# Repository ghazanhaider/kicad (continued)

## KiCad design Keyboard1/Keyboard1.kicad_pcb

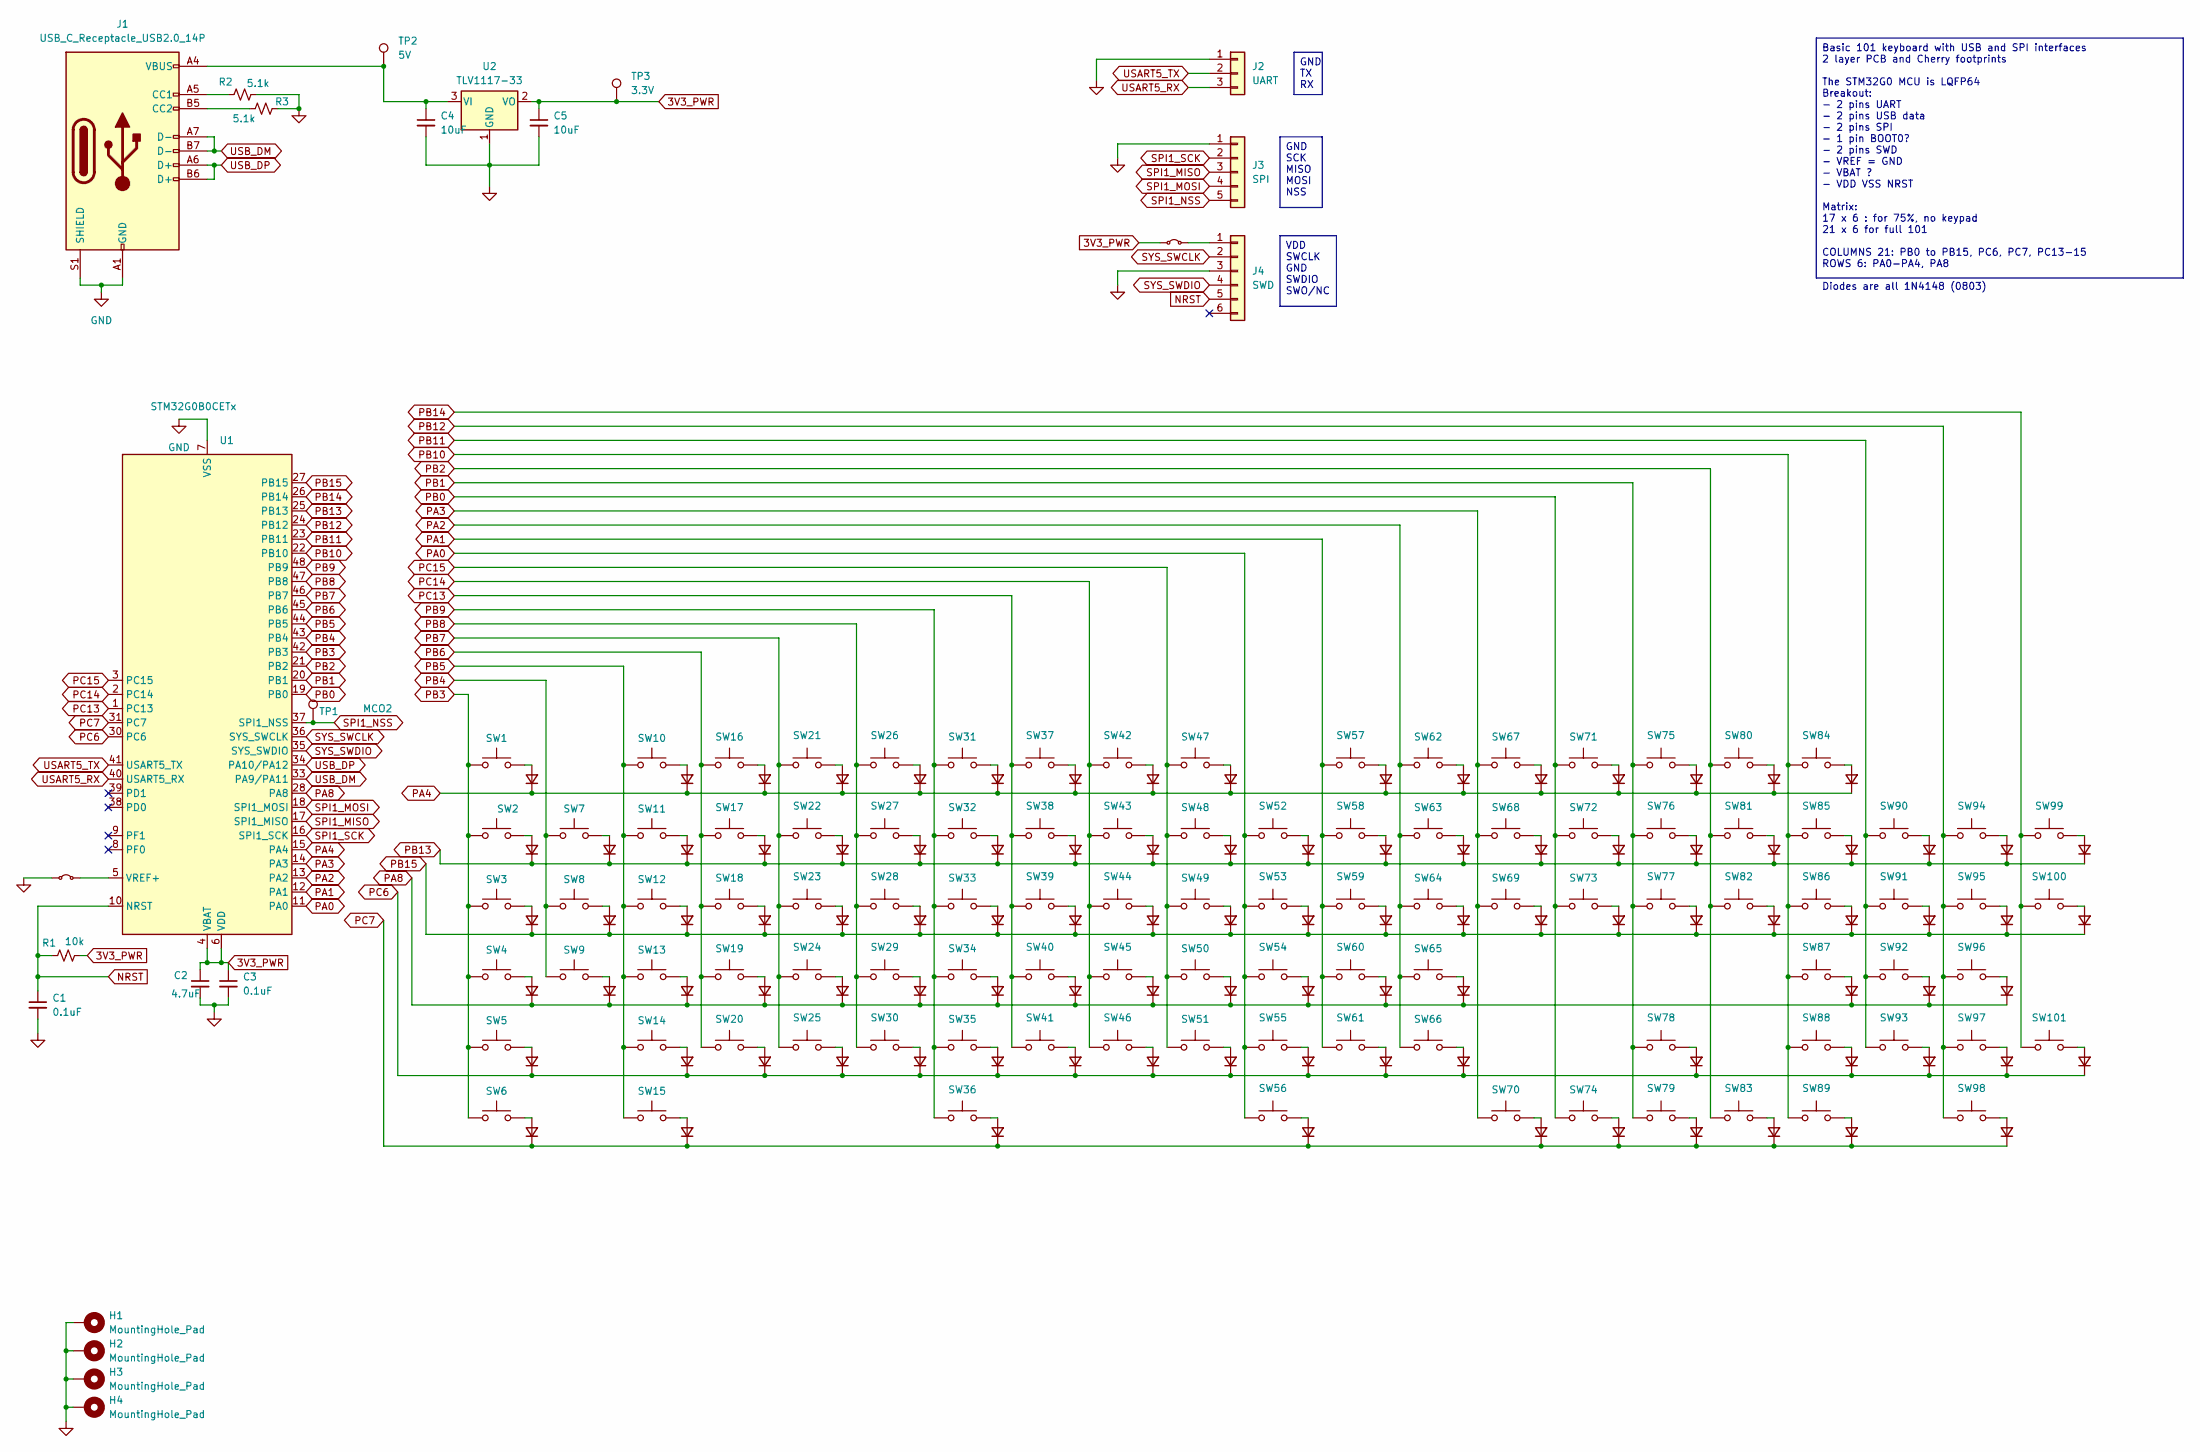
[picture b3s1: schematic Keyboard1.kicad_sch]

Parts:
C1, C3: 0.1uF; C_0603_1608Metric
C2: 4.7uF; C_0603_1608Metric
C4, C5: 10uF; C_0603_1608Metric
D1, D2, D3, D4, D5, D6, D7, D8, D9, D10, D11, D12, D13, D14, D15, D16, D17, D18, D19, D20, D21, D22, D23, D24, D25, D26, D27, D28, D29, D30, D31, D32, D33, D34, D35, D36, D37, D38, D39, D40, D41, D42, D43, D44, D45, D46, D47, D48, D49, D50, D51, D52, D53, D54, D55, D56, D57, D58, D59, D60, D61, D62, D63, D64, D65, D66, D67, D68, D69, D70, D71, D72, D73, D74, D75, D76, D77, D78, D79, D80, D81, D82, D83, D84, D85, D86, D87, D88, D89, D90, D91, D92, D93, D94, D95, D96, D97, D98, D99, D100, D101: D_Small; D_0805_2012Metric
H1, H2, H3, H4: MountingHole_Pad; MountingHole_2.7mm_M2.5_DIN965_Pad
J1: USB_C_Receptacle_USB2.0_14P; USB_C_Receptacle_GCT_USB4105-xx-A_16P_TopMnt_Horizontal
J2: UART; PinHeader_1x03_P2.54mm_Vertical
J3: SPI; PinHeader_1x05_P2.54mm_Vertical
J4: SWD; PinHeader_1x06_P2.54mm_Vertical
JP1, JP2: Jumper_2_Small_Bridged; SolderJumper-2_P1.3mm_Bridged_RoundedPad1.0x1.5mm
R1: 10k; R_0603_1608Metric
R2, R3: 5.1k; R_0603_1608Metric
SW1: SW_ESC?; SW_Cherry_MX_1.00u_PCB
SW2: SW_BACKTICK?; SW_Cherry_MX_1.00u_PCB
SW3: SW_TAB; SW_Cherry_MX_1.50u_PCB
SW4: SW_CAPS?; SW_Cherry_MX_1.75u_PCB
SW5: SW_LSHIFT?; SW_Cherry_MX_2.25u_PCB
SW6: SW_LCTRL?; SW_Cherry_MX_1.25u_PCB
SW7: SW_1; SW_Cherry_MX_1.00u_PCB
SW8: SW_Q; SW_Cherry_MX_1.00u_PCB
SW9: SW_A?; SW_Cherry_MX_1.00u_PCB
SW10: SW_F1; SW_Cherry_MX_1.00u_PCB
SW11: SW_2; SW_Cherry_MX_1.00u_PCB
SW12: SW_W; SW_Cherry_MX_1.00u_PCB
SW13: SW_S; SW_Cherry_MX_1.00u_PCB
SW14: SW_Z; SW_Cherry_MX_1.00u_PCB
SW15: SW_LALT?; SW_Cherry_MX_1.25u_PCB
SW16: SW_F2; SW_Cherry_MX_1.00u_PCB
SW17: SW_3; SW_Cherry_MX_1.00u_PCB
SW18: SW_E?; SW_Cherry_MX_1.00u_PCB
SW19: SW_D?; SW_Cherry_MX_1.00u_PCB
SW20: SW_X; SW_Cherry_MX_1.00u_PCB
SW21: SW_F3; SW_Cherry_MX_1.00u_PCB
SW22: SW_4; SW_Cherry_MX_1.00u_PCB
SW23: SW_R; SW_Cherry_MX_1.00u_PCB
SW24: SW_F?; SW_Cherry_MX_1.00u_PCB
SW25: SW_C?; SW_Cherry_MX_1.00u_PCB
SW26: SW_F4; SW_Cherry_MX_1.00u_PCB
SW27: SW_5; SW_Cherry_MX_1.00u_PCB
SW28: SW_T; SW_Cherry_MX_1.00u_PCB
SW29: SW_G?; SW_Cherry_MX_1.00u_PCB
SW30: SW_V; SW_Cherry_MX_1.00u_PCB
SW31: SW_F5; SW_Cherry_MX_1.00u_PCB
SW32: SW_6; SW_Cherry_MX_1.00u_PCB
SW33: SW_Y; SW_Cherry_MX_1.00u_PCB
SW34: SW_H?; SW_Cherry_MX_1.00u_PCB
SW35: SW_B?; SW_Cherry_MX_1.00u_PCB
SW36: SW_SPACE; SW_Cherry_MX_6.25u_PCB
SW37: SW_F6; SW_Cherry_MX_1.00u_PCB
SW38: SW_7; SW_Cherry_MX_1.00u_PCB
SW39: SW_U; SW_Cherry_MX_1.00u_PCB
SW40: SW_J?; SW_Cherry_MX_1.00u_PCB
SW41: SW_N?; SW_Cherry_MX_1.00u_PCB
SW42: SW_F7; SW_Cherry_MX_1.00u_PCB
SW43: SW_8; SW_Cherry_MX_1.00u_PCB
SW44: SW_I?; SW_Cherry_MX_1.00u_PCB
SW45: SW_K?; SW_Cherry_MX_1.00u_PCB
SW46: SW_M?; SW_Cherry_MX_1.00u_PCB
SW47: SW_F8; SW_Cherry_MX_1.00u_PCB
SW48: SW_9; SW_Cherry_MX_1.00u_PCB
SW49: SW_O; SW_Cherry_MX_1.00u_PCB
SW50: SW_L?; SW_Cherry_MX_1.00u_PCB
SW51: SW_COMMA?; SW_Cherry_MX_1.00u_PCB
SW52: SW_0; SW_Cherry_MX_1.00u_PCB
SW53: SW_P; SW_Cherry_MX_1.00u_PCB
SW54: SW_SCOLON; SW_Cherry_MX_1.00u_PCB
SW55: SW_DOT?; SW_Cherry_MX_1.00u_PCB
SW56: SW_RALT; SW_Cherry_MX_1.25u_PCB
SW57: SW_F9; SW_Cherry_MX_1.00u_PCB
SW58: SW_MINUS?; SW_Cherry_MX_1.00u_PCB
SW59: SW_LSQUARE?; SW_Cherry_MX_1.00u_PCB
SW60: SW_TICK; SW_Cherry_MX_1.00u_PCB
SW61: SW_SLASH; SW_Cherry_MX_1.00u_PCB
SW62: SW_F10; SW_Cherry_MX_1.00u_PCB
SW63: SW_PLUS; SW_Cherry_MX_1.00u_PCB
SW64: SW_RSQUARE; SW_Cherry_MX_1.00u_PCB
SW65: SW_ENTER?; SW_Cherry_MX_2.25u_PCB
SW66: SW_RSHIFT; SW_Cherry_MX_2.75u_PCB
SW67: SW_F11; SW_Cherry_MX_1.00u_PCB
SW68: SW_BACKSPACE?; SW_Cherry_MX_2.00u_PCB
SW69: SW_BSLASH?; SW_Cherry_MX_1.50u_PCB
SW70: SW_RCTRL; SW_Cherry_MX_1.25u_PCB
SW71: SW_F12; SW_Cherry_MX_1.00u_PCB
SW72: SW_INS?; SW_Cherry_MX_1.00u_PCB
SW73: SW_DELETE?; SW_Cherry_MX_1.00u_PCB
SW74: SW_LARROW?; SW_Cherry_MX_1.00u_PCB
SW75: SW_PRTSC; SW_Cherry_MX_1.00u_PCB
SW76: SW_HOME?; SW_Cherry_MX_1.00u_PCB
SW77: SW_END?; SW_Cherry_MX_1.00u_PCB
SW78: SW_UPARROW; SW_Cherry_MX_1.00u_PCB
SW79: SW_DARROW?; SW_Cherry_MX_1.00u_PCB
SW80: SW_SCRLK; SW_Cherry_MX_1.00u_PCB
SW81: SW_PGUP; SW_Cherry_MX_1.00u_PCB
SW82: SW_PGDN; SW_Cherry_MX_1.00u_PCB
SW83: SW_RARROW; SW_Cherry_MX_1.00u_PCB
SW84: SW_PAUSE; SW_Cherry_MX_1.00u_PCB
SW85: SW_NUMLOCK; SW_Cherry_MX_1.00u_PCB
SW86: SW_NP7; SW_Cherry_MX_1.00u_PCB
SW87: SW_NP4; SW_Cherry_MX_1.00u_PCB
SW88: SW_NP1; SW_Cherry_MX_1.00u_PCB
SW89: SW_NPINSERT; SW_Cherry_MX_2.00u_PCB
SW90: SW_NPSLASH; SW_Cherry_MX_1.00u_PCB
SW91: SW_NP8; SW_Cherry_MX_1.00u_PCB
SW92: SW_NP5; SW_Cherry_MX_1.00u_PCB
SW93: SW_NP2; SW_Cherry_MX_1.00u_PCB
SW94: SW_NPSTAR; SW_Cherry_MX_1.00u_PCB
SW95: SW_NP9; SW_Cherry_MX_1.00u_PCB
SW96: SW_NP6; SW_Cherry_MX_1.00u_PCB
SW97: SW_NP3; SW_Cherry_MX_1.00u_PCB
SW98: SW_NPDOT; SW_Cherry_MX_1.00u_PCB
SW99: SW_NPMINUS; SW_Cherry_MX_1.00u_PCB
SW100: SW_NPPLUS; SW_Cherry_MX_2.00u_Vertical_PCB
SW101: SW_NPENTER; SW_Cherry_MX_2.00u_Vertical_PCB
TP1: MCO2; TestPoint_Loop_D2.54mm_Drill1.5mm_Beaded
TP2: 5V; TestPoint_Loop_D2.54mm_Drill1.5mm_Beaded
TP3: 3.3V; TestPoint_Loop_D2.54mm_Drill1.5mm_Beaded
U1: STM32G0B0CETx; LQFP-48_7x7mm_P0.5mm
U2: TLV1117-33; SOT-223

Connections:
3V3_PWR: C2.1, C3.1, C5.1, JP2.1 (A), R1.2, TP3.1, U1.4 (VBAT), U1.6 (VDD), U2.2 (VO)
GND: C1.2, C2.2, C3.2, C4.2, C5.2, H1.1, H2.1, H3.1, H4.1, J1.A1 (GND), J1.A12 (GND), J1.B1 (GND), J1.B12 (GND), J1.S1 (SHIELD), J2.1, J3.1, J4.3, JP1.1 (A), R2.2, R3.2, U1.7 (VSS), U2.1 (GND)
NRST: C1.1, J4.5, R1.1, U1.10 (NRST)
unnamed: D1.2 (A), SW1.2
unnamed: D2.2 (A), SW2.2
unnamed: D3.2 (A), SW3.2
unnamed: D4.2 (A), SW4.2
unnamed: D5.2 (A), SW5.2
unnamed: D6.2 (A), SW6.2
unnamed: D7.2 (A), SW7.2
unnamed: D8.2 (A), SW8.2
unnamed: D9.2 (A), SW9.2
unnamed: D10.2 (A), SW10.2
unnamed: D11.2 (A), SW11.2
unnamed: D12.2 (A), SW12.2
unnamed: D13.2 (A), SW13.2
unnamed: D14.2 (A), SW14.2
unnamed: D15.2 (A), SW15.2
unnamed: D16.2 (A), SW16.2
unnamed: D17.2 (A), SW17.2
unnamed: D18.2 (A), SW18.2
unnamed: D19.2 (A), SW19.2
unnamed: D20.2 (A), SW20.2
unnamed: D21.2 (A), SW21.2
unnamed: D22.2 (A), SW22.2
unnamed: D23.2 (A), SW23.2
unnamed: D24.2 (A), SW24.2
unnamed: D25.2 (A), SW25.2
unnamed: D26.2 (A), SW26.2
unnamed: D27.2 (A), SW27.2
unnamed: D28.2 (A), SW28.2
unnamed: D29.2 (A), SW29.2
unnamed: D30.2 (A), SW30.2
unnamed: D31.2 (A), SW31.2
unnamed: D32.2 (A), SW32.2
unnamed: D33.2 (A), SW33.2
unnamed: D34.2 (A), SW34.2
unnamed: D35.2 (A), SW35.2
unnamed: D36.2 (A), SW36.2
unnamed: D37.2 (A), SW37.2
unnamed: D38.2 (A), SW38.2
unnamed: D39.2 (A), SW39.2
unnamed: D40.2 (A), SW40.2
unnamed: D41.2 (A), SW41.2
unnamed: D42.2 (A), SW42.2
unnamed: D43.2 (A), SW43.2
unnamed: D44.2 (A), SW44.2
unnamed: D45.2 (A), SW45.2
unnamed: D46.2 (A), SW46.2
unnamed: D47.2 (A), SW47.2
unnamed: D48.2 (A), SW48.2
unnamed: D49.2 (A), SW49.2
unnamed: D50.2 (A), SW50.2
unnamed: D51.2 (A), SW51.2
unnamed: D52.2 (A), SW52.2
unnamed: D53.2 (A), SW53.2
unnamed: D54.2 (A), SW54.2
unnamed: D55.2 (A), SW55.2
unnamed: D56.2 (A), SW56.2
unnamed: D57.2 (A), SW57.2
unnamed: D58.2 (A), SW58.2
unnamed: D59.2 (A), SW59.2
unnamed: D60.2 (A), SW60.2
unnamed: D61.2 (A), SW61.2
unnamed: D62.2 (A), SW62.2
unnamed: D63.2 (A), SW63.2
unnamed: D64.2 (A), SW64.2
unnamed: D65.2 (A), SW65.2
unnamed: D66.2 (A), SW66.2
unnamed: D67.2 (A), SW67.2
unnamed: D68.2 (A), SW68.2
unnamed: D69.2 (A), SW69.2
unnamed: D70.2 (A), SW70.2
unnamed: D71.2 (A), SW71.2
unnamed: D72.2 (A), SW72.2
unnamed: D73.2 (A), SW73.2
unnamed: D74.2 (A), SW74.2
unnamed: D75.2 (A), SW75.2
unnamed: D76.2 (A), SW76.2
unnamed: D77.2 (A), SW77.2
unnamed: D78.2 (A), SW78.2
unnamed: D79.2 (A), SW79.2
unnamed: D80.2 (A), SW80.2
unnamed: D81.2 (A), SW81.2
unnamed: D82.2 (A), SW82.2
unnamed: D83.2 (A), SW83.2
unnamed: D84.2 (A), SW84.2
unnamed: D85.2 (A), SW85.2
unnamed: D86.2 (A), SW86.2
unnamed: D87.2 (A), SW87.2
unnamed: D88.2 (A), SW88.2
unnamed: D89.2 (A), SW89.2
unnamed: D90.2 (A), SW90.2
unnamed: D91.2 (A), SW91.2
unnamed: D92.2 (A), SW92.2
unnamed: D93.2 (A), SW93.2
unnamed: D94.2 (A), SW94.2
unnamed: D95.2 (A), SW95.2
unnamed: D96.2 (A), SW96.2
unnamed: D97.2 (A), SW97.2
unnamed: D98.2 (A), SW98.2
unnamed: D99.2 (A), SW99.2
unnamed: D100.2 (A), SW100.2
unnamed: D101.2 (A), SW101.2
unnamed: J1.A5 (CC1), R2.1
unnamed: J1.B5 (CC2), R3.1
unnamed: J4.1, JP2.2 (B)
unnamed: JP1.2 (B), U1.5 (VREF+)
unnamed: C4.1, J1.A4 (VBUS), J1.A9 (VBUS), J1.B4 (VBUS), J1.B9 (VBUS), TP2.1, U2.3 (VI)
PA0: SW52.1, SW53.1, SW54.1, SW55.1, SW56.1, U1.11 (PA0)
PA1: SW57.1, SW58.1, SW59.1, SW60.1, SW61.1, U1.12 (PA1)
PA2: SW62.1, SW63.1, SW64.1, SW65.1, SW66.1, U1.13 (PA2)
PA3: SW67.1, SW68.1, SW69.1, SW70.1, U1.14 (PA3)
PA4: D1.1 (K), D10.1 (K), D16.1 (K), D21.1 (K), D26.1 (K), D31.1 (K), D37.1 (K), D42.1 (K), D47.1 (K), D57.1 (K), D62.1 (K), D67.1 (K), D71.1 (K), D75.1 (K), D80.1 (K), D84.1 (K), U1.15 (PA4)
PA8: D4.1 (K), D9.1 (K), D13.1 (K), D19.1 (K), D24.1 (K), D29.1 (K), D34.1 (K), D40.1 (K), D45.1 (K), D50.1 (K), D54.1 (K), D60.1 (K), D65.1 (K), D87.1 (K), D92.1 (K), D96.1 (K), U1.28 (PA8)
PB0: SW71.1, SW72.1, SW73.1, SW74.1, U1.19 (PB0)
PB1: SW75.1, SW76.1, SW77.1, SW78.1, SW79.1, U1.20 (PB1)
PB2: SW80.1, SW81.1, SW82.1, SW83.1, U1.21 (PB2)
PB3: SW1.1, SW2.1, SW3.1, SW4.1, SW5.1, SW6.1, U1.42 (PB3)
PB4: SW7.1, SW8.1, SW9.1, U1.43 (PB4)
PB5: SW10.1, SW11.1, SW12.1, SW13.1, SW14.1, SW15.1, U1.44 (PB5)
PB6: SW16.1, SW17.1, SW18.1, SW19.1, SW20.1, U1.45 (PB6)
PB7: SW21.1, SW22.1, SW23.1, SW24.1, SW25.1, U1.46 (PB7)
PB8: SW26.1, SW27.1, SW28.1, SW29.1, SW30.1, U1.47 (PB8)
PB9: SW31.1, SW32.1, SW33.1, SW34.1, SW35.1, SW36.1, U1.48 (PB9)
PB10: SW84.1, SW85.1, SW86.1, SW87.1, SW88.1, SW89.1, U1.22 (PB10)
PB11: SW90.1, SW91.1, SW92.1, SW93.1, U1.23 (PB11)
PB12: SW94.1, SW95.1, SW96.1, SW97.1, SW98.1, U1.24 (PB12)
PB13: D2.1 (K), D7.1 (K), D11.1 (K), D17.1 (K), D22.1 (K), D27.1 (K), D32.1 (K), D38.1 (K), D43.1 (K), D48.1 (K), D52.1 (K), D58.1 (K), D63.1 (K), D68.1 (K), D72.1 (K), D76.1 (K), D81.1 (K), D85.1 (K), D90.1 (K), D94.1 (K), D99.1 (K), U1.25 (PB13)
PB14: SW99.1, SW100.1, SW101.1, U1.26 (PB14)
PB15: D3.1 (K), D8.1 (K), D12.1 (K), D18.1 (K), D23.1 (K), D28.1 (K), D33.1 (K), D39.1 (K), D44.1 (K), D49.1 (K), D53.1 (K), D59.1 (K), D64.1 (K), D69.1 (K), D73.1 (K), D77.1 (K), D82.1 (K), D86.1 (K), D91.1 (K), D95.1 (K), D100.1 (K), U1.27 (PB15)
PC6: D5.1 (K), D14.1 (K), D20.1 (K), D25.1 (K), D30.1 (K), D35.1 (K), D41.1 (K), D46.1 (K), D51.1 (K), D55.1 (K), D61.1 (K), D66.1 (K), D78.1 (K), D88.1 (K), D93.1 (K), D97.1 (K), D101.1 (K), U1.30 (PC6)
PC7: D6.1 (K), D15.1 (K), D36.1 (K), D56.1 (K), D70.1 (K), D74.1 (K), D79.1 (K), D83.1 (K), D89.1 (K), D98.1 (K), U1.31 (PC7)
PC13: SW37.1, SW38.1, SW39.1, SW40.1, SW41.1, U1.1 (PC13)
PC14: SW42.1, SW43.1, SW44.1, SW45.1, SW46.1, U1.2 (PC14)
PC15: SW47.1, SW48.1, SW49.1, SW50.1, SW51.1, U1.3 (PC15)
SPI1_MISO: J3.3, U1.17 (SPI1_MISO)
SPI1_MOSI: J3.4, U1.18 (SPI1_MOSI)
SPI1_NSS: J3.5, TP1.1, U1.37 (SPI1_NSS)
SPI1_SCK: J3.2, U1.16 (SPI1_SCK)
SYS_SWCLK: J4.2, U1.36 (SYS_SWCLK)
SYS_SWDIO: J4.4, U1.35 (SYS_SWDIO)
USART5_RX: J2.3, U1.40 (USART5_RX)
USART5_TX: J2.2, U1.41 (USART5_TX)
USB_DM: J1.A7 (D-), J1.B7 (D-), U1.33 (PA9/PA11)
USB_DP: J1.A6 (D+), J1.B6 (D+), U1.34 (PA10/PA12)

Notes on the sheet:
VDD SWCLK GND SWDIO SWO/NC
GND TX RX
Basic 101 keyboard with USB and SPI interfaces 2 layer PCB and Cherry footprints The STM32G0 MCU is LQFP64 Breakout: - 2 pins UART - 2 pins USB data - 2 pins SPI - 1 pin BOOT0? - 2 pins SWD - VREF = GND - VBAT ? - VDD VSS NRST Matrix: 17 x 6 : for 75%, no keypad 21 x 6 for full 101 COLUMNS 21: PB0 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
GND SCK MISO MOSI NSS

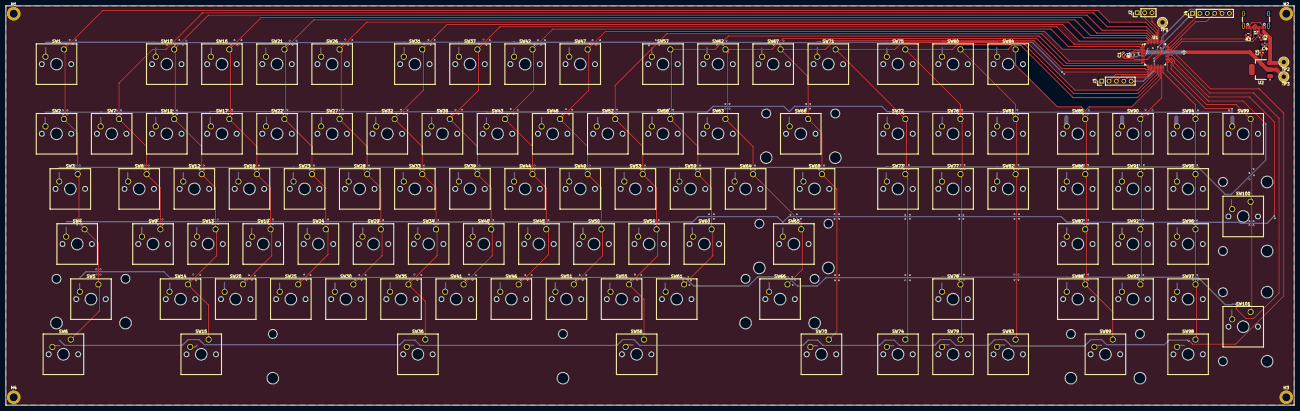
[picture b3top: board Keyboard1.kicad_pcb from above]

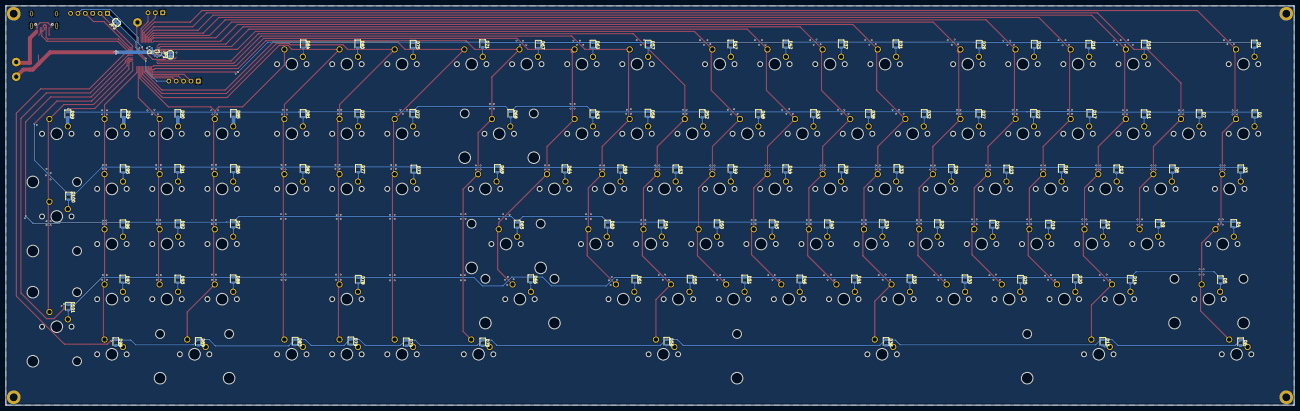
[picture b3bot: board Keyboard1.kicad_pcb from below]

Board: 2 copper layers, 444.0 x 137.6 mm, 225 parts (105 on the bottom side), 146 nets.

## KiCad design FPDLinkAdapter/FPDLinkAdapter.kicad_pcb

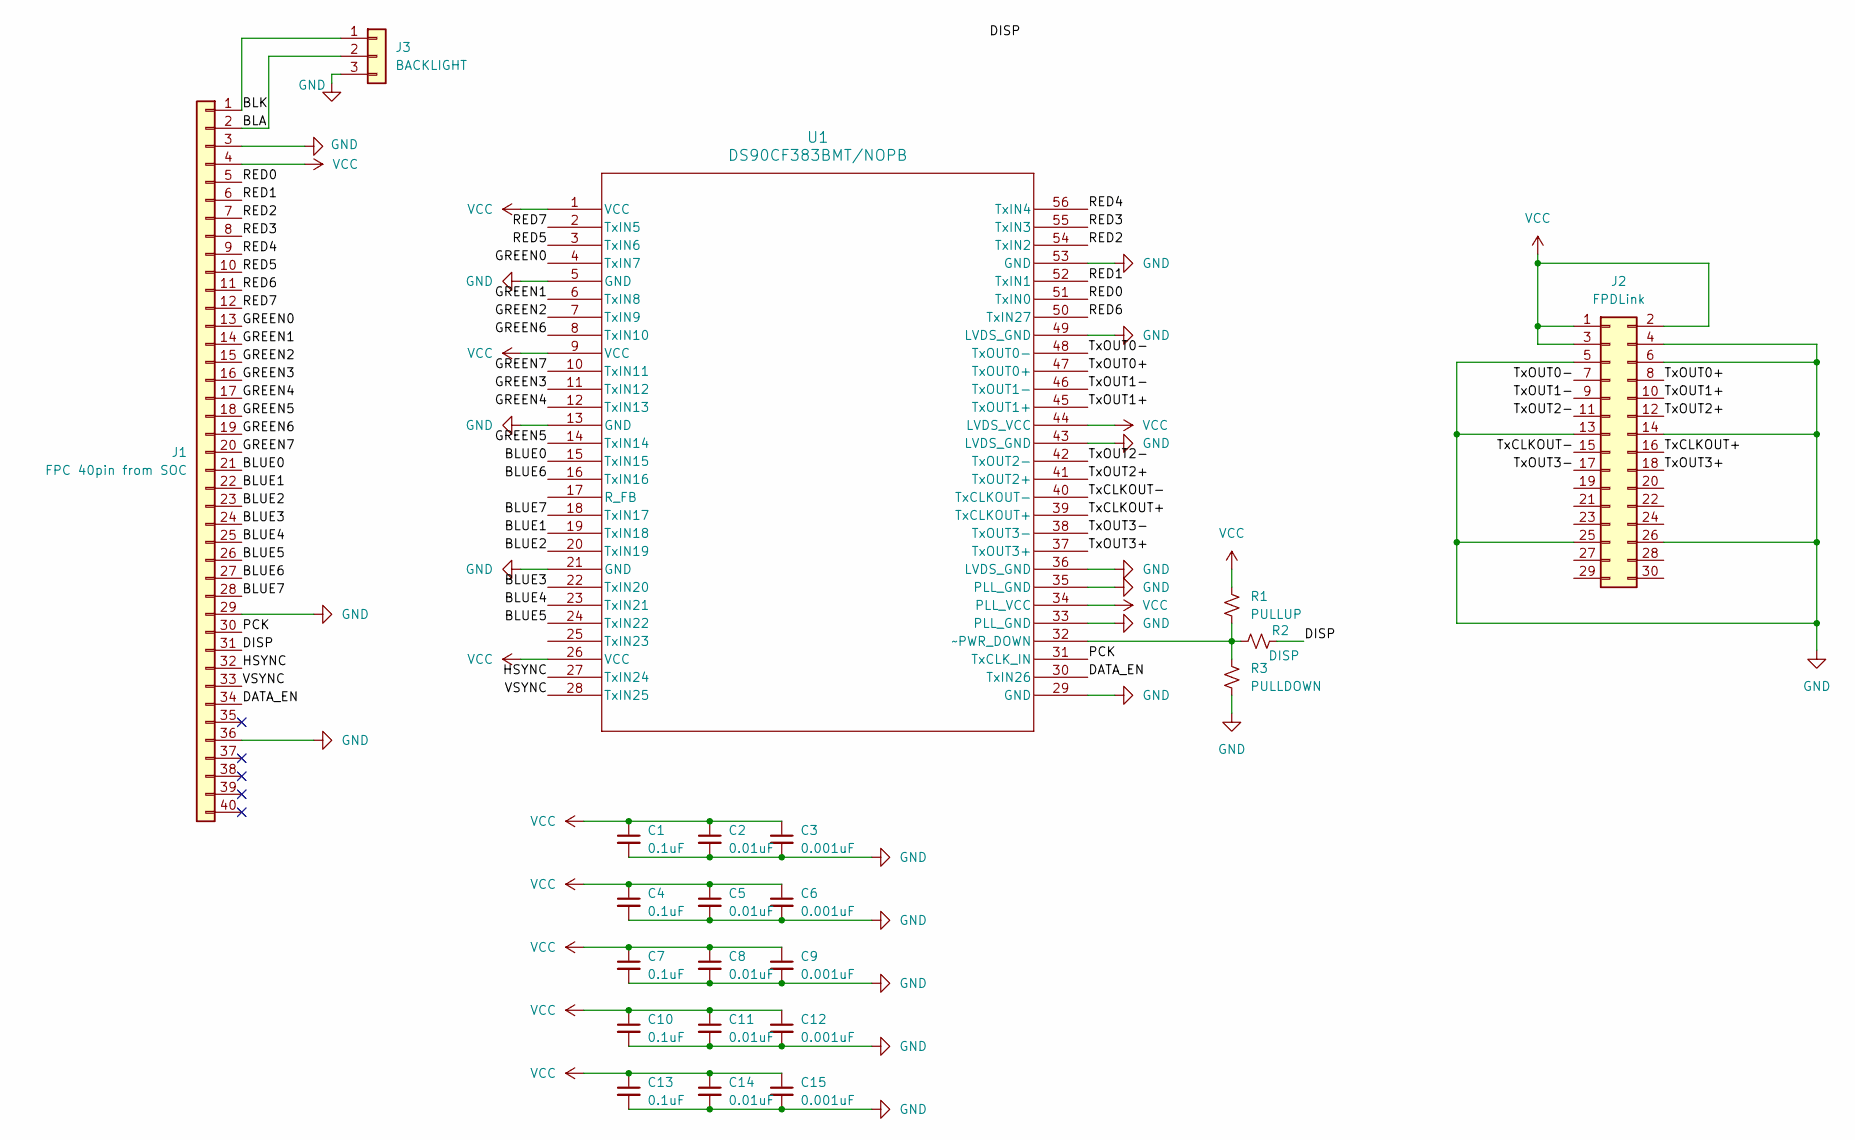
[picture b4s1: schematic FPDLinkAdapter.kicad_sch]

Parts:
C1, C4, C7, C10, C13: 0.1uF; C_0805_2012Metric
C2, C5, C8, C11, C14: 0.01uF; C_0805_2012Metric
C3, C6, C9, C12, C15: 0.001uF; C_0805_2012Metric
J1: FPC 40pin from SOC; Hirose_FH12-40S-0.5SH_1x40-1MP_P0.50mm_Horizontal
J2: FPDLink; PinHeader_2x15_P2.00mm_Vertical
J3: BACKLIGHT; PinSocket_1x03_P2.54mm_Vertical
R1: PULLUP; R_0805_2012Metric
R2: DISP; R_0805_2012Metric
R3: PULLDOWN; R_0805_2012Metric
U1: DS90CF383BMT/NOPB; MTD56_TEX

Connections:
/BLA: J1.2, J3.2
/BLK: J1.1, J3.1
/BLUE0: J1.21, U1.15 (TxIN15)
/BLUE1: J1.22, U1.19 (TxIN18)
/BLUE2: J1.23, U1.20 (TxIN19)
/BLUE3: J1.24, U1.22 (TxIN20)
/BLUE4: J1.25, U1.23 (TxIN21)
/BLUE5: J1.26, U1.24 (TxIN22)
/BLUE6: J1.27, U1.16 (TxIN16)
/BLUE7: J1.28, U1.18 (TxIN17)
/DATA_EN: J1.34, U1.30 (TxIN26)
/DISP: J1.31, R2.2
/GREEN0: J1.13, U1.4 (TxIN7)
/GREEN1: J1.14, U1.6 (TxIN8)
/GREEN2: J1.15, U1.7 (TxIN9)
/GREEN3: J1.16, U1.11 (TxIN12)
/GREEN4: J1.17, U1.12 (TxIN13)
/GREEN5: J1.18, U1.14 (TxIN14)
/GREEN6: J1.19, U1.8 (TxIN10)
/GREEN7: J1.20, U1.10 (TxIN11)
/HSYNC: J1.32, U1.27 (TxIN24)
/PCK: J1.30, U1.31 (TxCLK_IN)
/RED0: J1.5, U1.51 (TxIN0)
/RED1: J1.6, U1.52 (TxIN1)
/RED2: J1.7, U1.54 (TxIN2)
/RED3: J1.8, U1.55 (TxIN3)
/RED4: J1.9, U1.56 (TxIN4)
/RED5: J1.10, U1.3 (TxIN6)
/RED6: J1.11, U1.50 (TxIN27)
/RED7: J1.12, U1.2 (TxIN5)
/TxCLKOUT+: J2.16, U1.39 (TxCLKOUT+)
/TxCLKOUT-: J2.15, U1.40 (TxCLKOUT-)
/TxOUT0+: J2.8, U1.47 (TxOUT0+)
/TxOUT0-: J2.7, U1.48 (TxOUT0-)
/TxOUT1+: J2.10, U1.45 (TxOUT1+)
/TxOUT1-: J2.9, U1.46 (TxOUT1-)
/TxOUT2+: J2.12, U1.41 (TxOUT2+)
/TxOUT2-: J2.11, U1.42 (TxOUT2-)
/TxOUT3+: J2.18, U1.37 (TxOUT3+)
/TxOUT3-: J2.17, U1.38 (TxOUT3-)
/VSYNC: J1.33, U1.28 (TxIN25)
GND: C1.2, C2.2, C3.2, C4.2, C5.2, C6.2, C7.2, C8.2, C9.2, C10.2, C11.2, C12.2, C13.2, C14.2, C15.2, J1.3, J1.29, J1.36, J2.4, J2.5, J2.6, J2.13, J2.14, J2.25, J2.26, J3.3, R3.2, U1.5 (GND), U1.13 (GND), U1.21 (GND), U1.29 (GND), U1.33 (PLL_GND), U1.35 (PLL_GND), U1.36 (LVDS_GND), U1.43 (LVDS_GND), U1.49 (LVDS_GND), U1.53 (GND)
unnamed: R1.2, R2.1, R3.1, U1.32 (~PWR_DOWN)
VCC: C1.1, C2.1, C3.1, C4.1, C5.1, C6.1, C7.1, C8.1, C9.1, C10.1, C11.1, C12.1, C13.1, C14.1, C15.1, J1.4, J2.1, J2.2, J2.3, R1.1, U1.1 (VCC), U1.9 (VCC), U1.26 (VCC), U1.34 (PLL_VCC), U1.44 (LVDS_VCC)

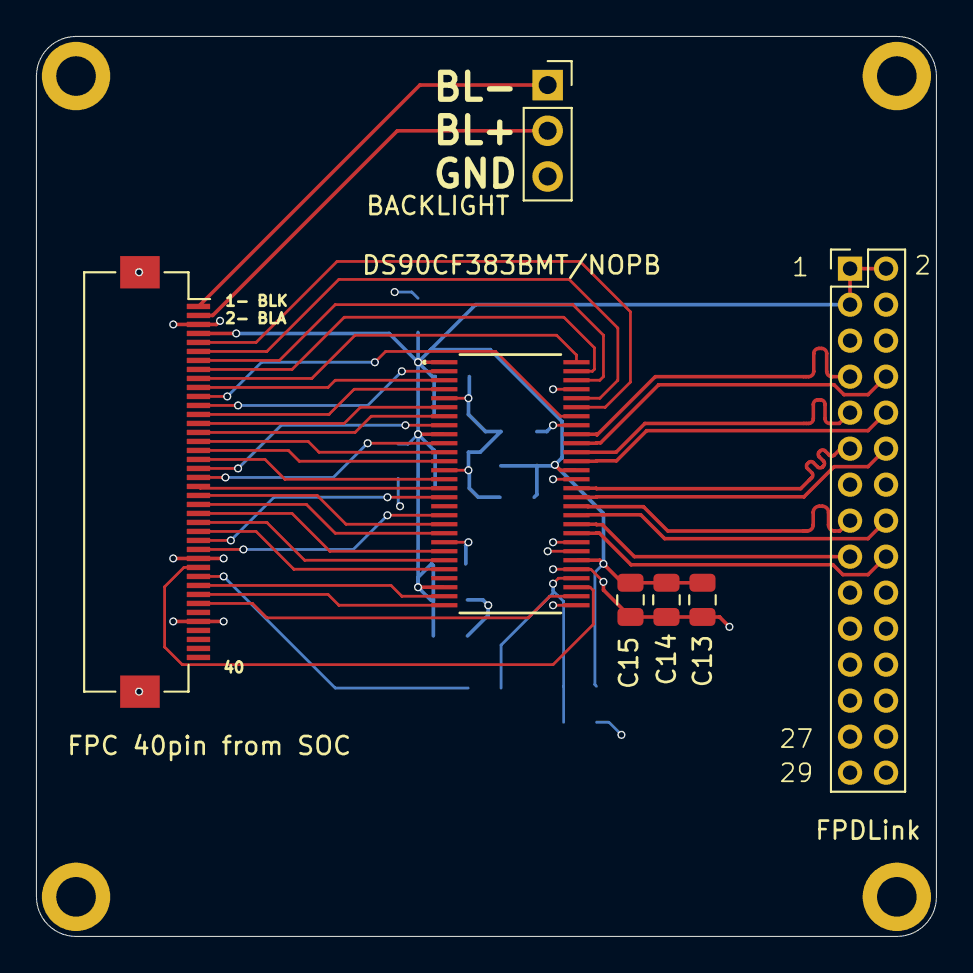
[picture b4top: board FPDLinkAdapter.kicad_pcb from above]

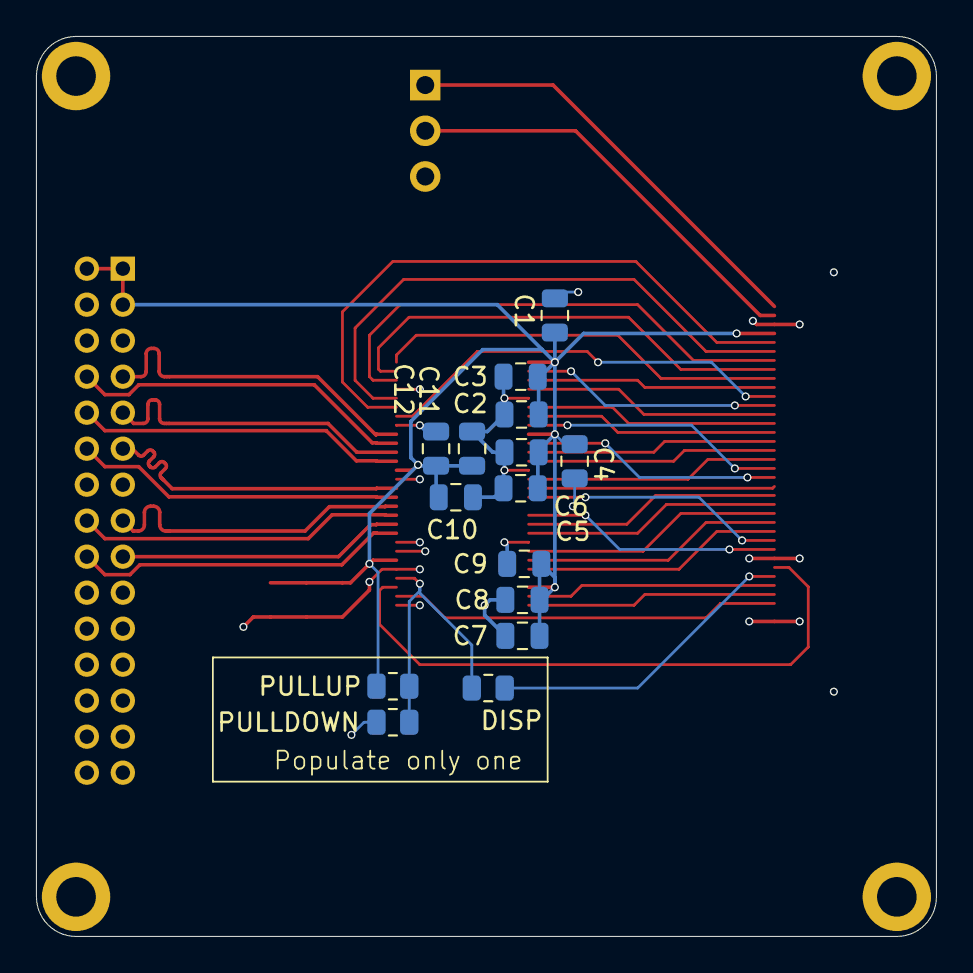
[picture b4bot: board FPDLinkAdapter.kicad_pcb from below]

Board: 4 copper layers, 50.0 x 50.0 mm, 22 parts (15 on the bottom side), 44 nets.
